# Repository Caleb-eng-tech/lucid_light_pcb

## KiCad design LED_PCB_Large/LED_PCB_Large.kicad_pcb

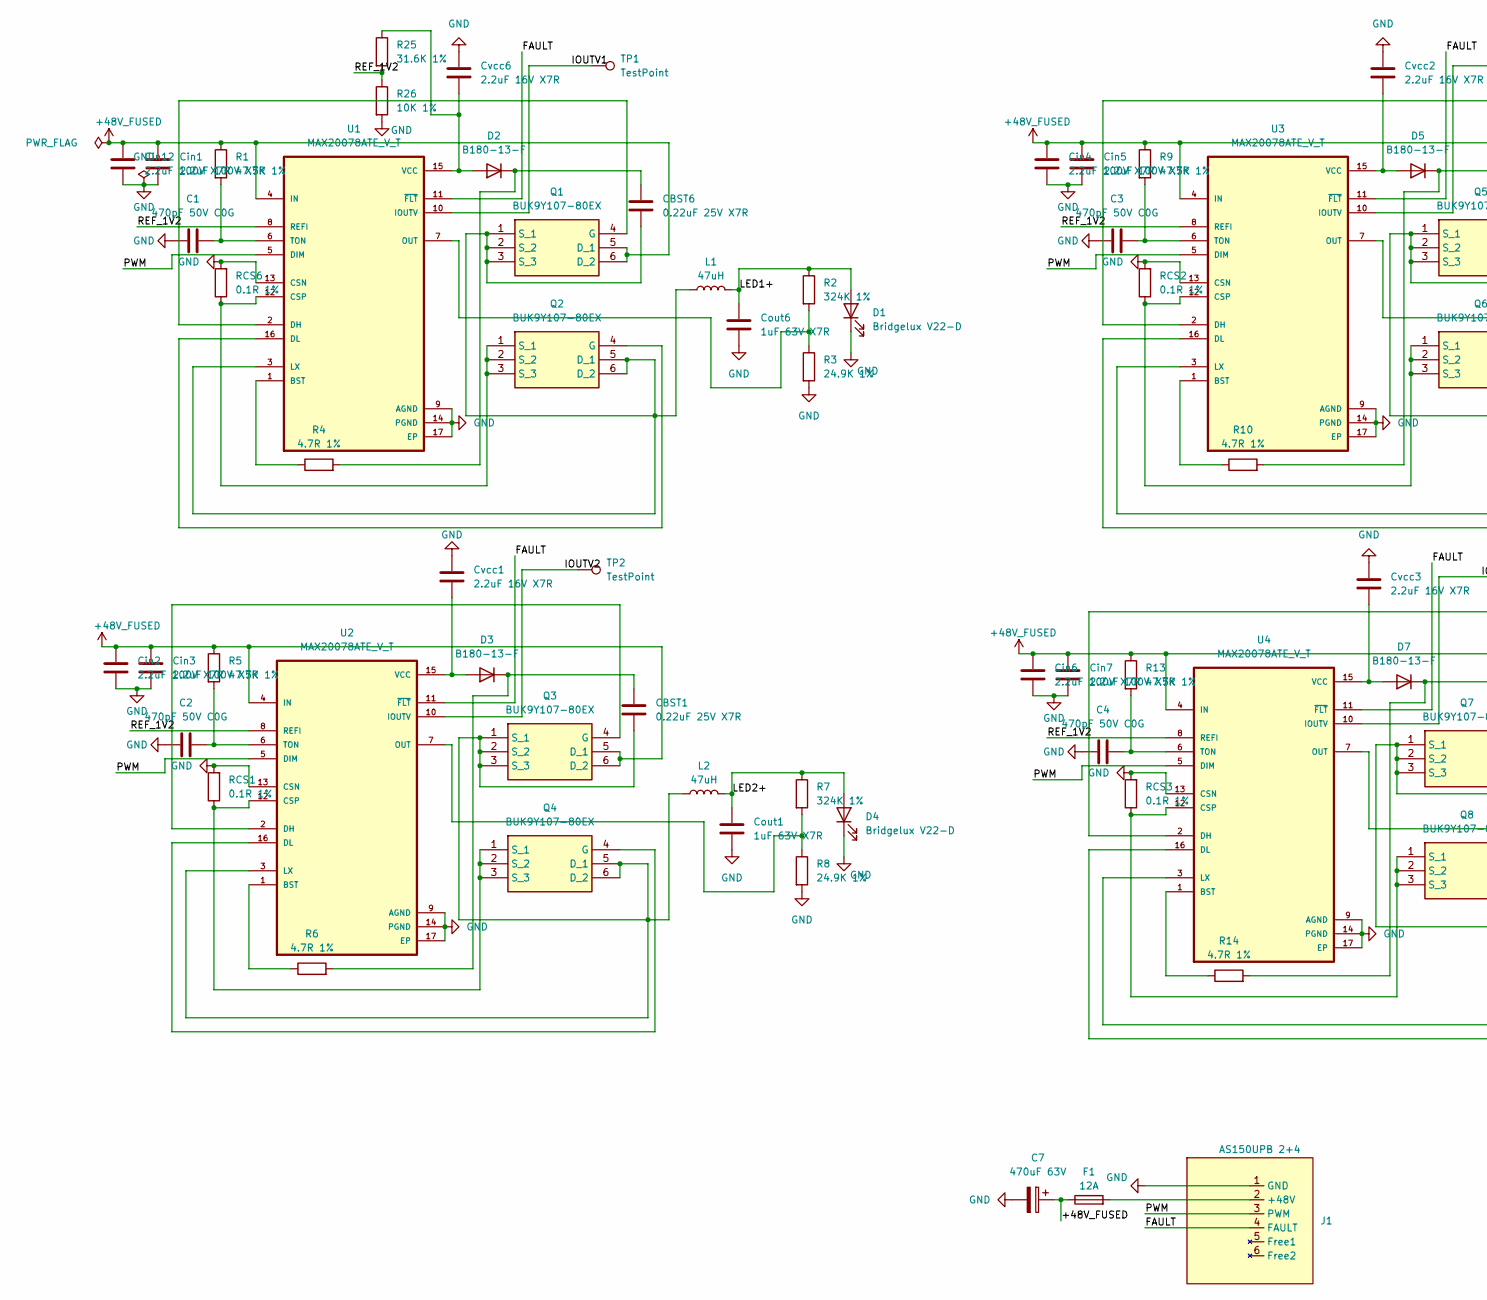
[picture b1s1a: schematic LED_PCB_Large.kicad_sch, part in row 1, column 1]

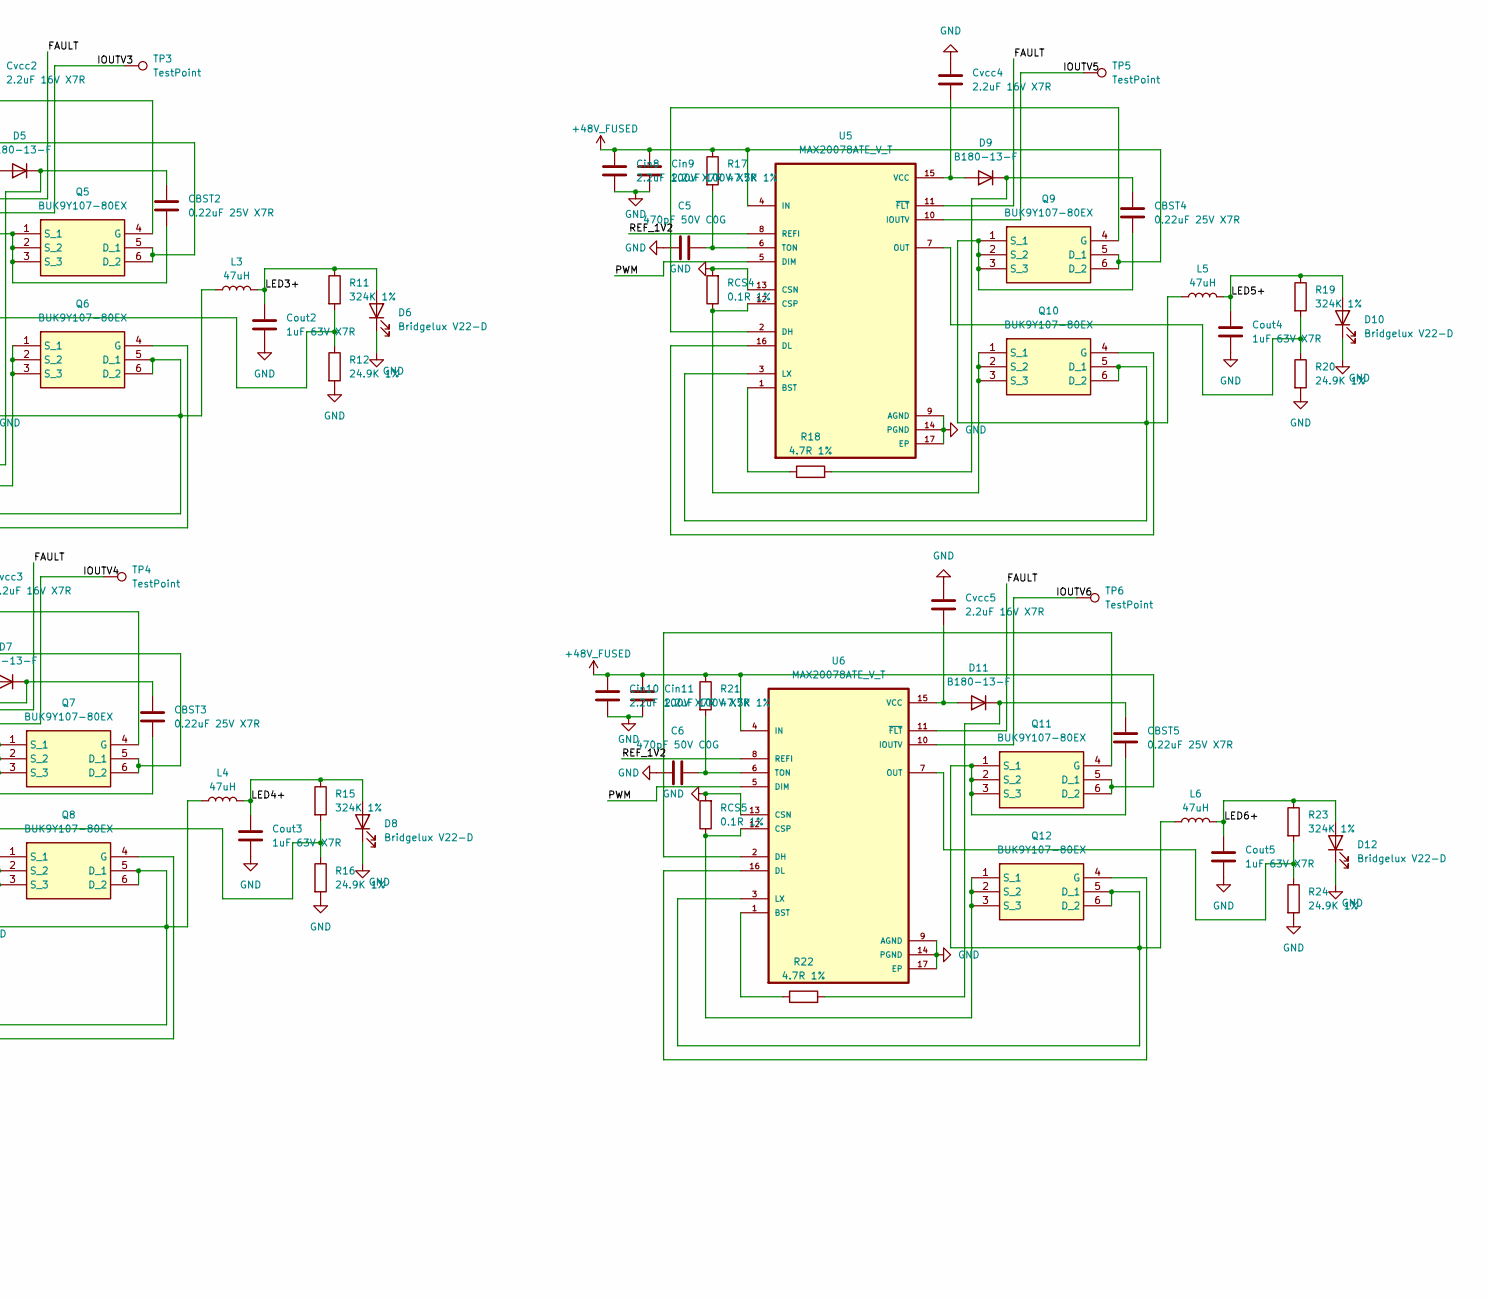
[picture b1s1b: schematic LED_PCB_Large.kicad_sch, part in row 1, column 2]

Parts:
C1, C2, C3, C4, C5, C6: 470pF 50V C0G; C_0603_1608Metric
C7: 470uF 63V; CP_Radial_D12.5mm_P5.00mm
CBST1, CBST2, CBST3, CBST4, CBST5, CBST6: 0.22uF 25V X7R; C_0603_1608Metric
Cin1, Cin2, Cin3, Cin4, Cin5, Cin6, Cin7, Cin8, Cin9, Cin10, Cin11, Cin12: 2.2uF 100V X7R; C_1210_3225Metric
Cout1, Cout2, Cout3, Cout4, Cout5, Cout6: 1uF 63V X7R; C_0805_2012Metric
Cvcc1, Cvcc2, Cvcc3, Cvcc4, Cvcc5, Cvcc6: 2.2uF 16V X7R; C_0805_2012Metric
D1, D4, D6, D8, D10, D12: Bridgelux V22-D; Bridgelux_V22_Custom
D2, D3, D5, D7, D9, D11: B180-13-F; D_SMA
F1: 12A; 0454012.MR
J1: AS150UPB 2+4; AS150UPB_2+4
L1, L2, L3, L4, L5, L6: 47uH; L_Coilcraft_MSS1278T-XXX
Q1, Q2, Q3, Q4, Q5, Q6, Q7, Q8, Q9, Q10, Q11, Q12: BUK9Y107-80EX; PHPT61002NYCLHX; Manufacturer_Part_Number BUK9Y107-80EX; Mouser Part Number 771-BUK9Y107-80EX
R1, R5, R9, R13, R17, R21: 47.5K 1%; R_0603_1608Metric
R2, R7, R11, R15, R19, R23: 324K 1%; R_0603_1608Metric
R3, R8, R12, R16, R20, R24: 24.9K 1%; R_0603_1608Metric
R4, R6, R10, R14, R18, R22: 4.7R 1%; R_0603_1608Metric
R25: 31.6K 1%; R_0603_1608Metric
R26: 10K 1%; R_0603_1608Metric
RCS1, RCS2, RCS3, RCS4, RCS5, RCS6: 0.1R 1%; R_1206_3216Metric
TP1, TP2, TP3, TP4, TP5, TP6: TestPoint; TestPoint_Pad_D1.0mm
U1, U2, U3, U4, U5, U6: MAX20078ATE_V_T; QFN50P300X300X80-17N

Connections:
+48V_FUSED: C7.1, Cin1.1, Cin2.1, Cin3.1, Cin4.1, Cin5.1, Cin6.1, Cin7.1, Cin8.1, Cin9.1, Cin10.1, Cin11.1, Cin12.1, F1.1, Q1.5 (D_1), Q1.6 (D_2), Q3.5 (D_1), Q3.6 (D_2), Q5.5 (D_1), Q5.6 (D_2), Q7.5 (D_1), Q7.6 (D_2), Q9.5 (D_1), Q9.6 (D_2), Q11.5 (D_1), Q11.6 (D_2), R1.1, R5.1, R9.1, R13.1, R17.1, R21.1, U1.4 (IN), U2.4 (IN), U3.4 (IN), U4.4 (IN), U5.4 (IN), U6.4 (IN)
/FAULT: J1.4 (FAULT), U1.11 (~FLT), U2.11 (~FLT), U3.11 (~FLT), U4.11 (~FLT), U5.11 (~FLT), U6.11 (~FLT)
/IOUTV1: TP1.1 (1_1), U1.10 (IOUTV)
/IOUTV2: TP2.1 (1_1), U2.10 (IOUTV)
/IOUTV3: TP3.1 (1_1), U3.10 (IOUTV)
/IOUTV4: TP4.1 (1_1), U4.10 (IOUTV)
/IOUTV5: TP5.1 (1_1), U5.10 (IOUTV)
/IOUTV6: TP6.1 (1_1), U6.10 (IOUTV)
/LED1+: Cout6.1, D1.2 (A), L1.2, R2.1
/LED2+: Cout1.1, D4.2 (A), L2.2, R7.1
/LED3+: Cout2.1, D6.2 (A), L3.2, R11.1
/LED4+: Cout3.1, D8.2 (A), L4.2, R15.1
/LED5+: Cout4.1, D10.2 (A), L5.2, R19.1
/LED6+: Cout5.1, D12.2 (A), L6.2, R23.1
/PWM: J1.3 (PWM), U1.5 (DIM), U2.5 (DIM), U3.5 (DIM), U4.5 (DIM), U5.5 (DIM), U6.5 (DIM)
/REF_1V2: R25.2, R26.1, U1.8 (REFI), U2.8 (REFI), U3.8 (REFI), U4.8 (REFI), U5.8 (REFI), U6.8 (REFI)
GND: C1.1, C2.1, C3.1, C4.1, C5.1, C6.1, C7.2, Cin1.2, Cin2.2, Cin3.2, Cin4.2, Cin5.2, Cin6.2, Cin7.2, Cin8.2, Cin9.2, Cin10.2, Cin11.2, Cin12.2, Cout1.2, Cout2.2, Cout3.2, Cout4.2, Cout5.2, Cout6.2, Cvcc1.1, Cvcc2.1, Cvcc3.1, Cvcc4.1, Cvcc5.1, Cvcc6.1, D1.1 (K), D4.1 (K), D6.1 (K), D8.1 (K), D10.1 (K), D12.1 (K), J1.1 (GND), R3.2, R8.2, R12.2, R16.2, R20.2, R24.2, R26.2, RCS1.2, RCS2.2, RCS3.2, RCS4.2, RCS5.2, RCS6.2, U1.9 (AGND), U1.13 (CSN), U1.14 (PGND), U1.17 (EP), U2.9 (AGND), U2.13 (CSN), U2.14 (PGND), U2.17 (EP), U3.9 (AGND), U3.13 (CSN), U3.14 (PGND), U3.17 (EP), U4.9 (AGND), U4.13 (CSN), U4.14 (PGND), U4.17 (EP), U5.9 (AGND), U5.13 (CSN), U5.14 (PGND), U5.17 (EP), U6.9 (AGND), U6.13 (CSN), U6.14 (PGND), U6.17 (EP)
unnamed: Cvcc6.2, D2.2 (A), R25.1, U1.15 (VCC)
unnamed: CBST6.1, D2.1 (K), R4.2
unnamed: Cvcc1.2, D3.2 (A), U2.15 (VCC)
unnamed: CBST1.1, D3.1 (K), R6.2
unnamed: Cvcc2.2, D5.2 (A), U3.15 (VCC)
unnamed: CBST2.1, D5.1 (K), R10.2
unnamed: Cvcc3.2, D7.2 (A), U4.15 (VCC)
unnamed: CBST3.1, D7.1 (K), R14.2
unnamed: Cvcc4.2, D9.2 (A), U5.15 (VCC)
unnamed: CBST4.1, D9.1 (K), R18.2
unnamed: Cvcc5.2, D11.2 (A), U6.15 (VCC)
unnamed: CBST5.1, D11.1 (K), R22.2
unnamed: F1.2, J1.2 (+48V)
unnamed: Q1.4 (G), U1.2 (DH)
unnamed: CBST6.2, L1.1, Q1.1 (S_1), Q1.2 (S_2), Q1.3 (S_3), Q2.5 (D_1), Q2.6 (D_2), U1.3 (LX)
unnamed: Q2.4 (G), U1.16 (DL)
unnamed: Q2.1 (S_1), Q2.2 (S_2), Q2.3 (S_3), RCS6.1, U1.12 (CSP)
unnamed: Q3.4 (G), U2.2 (DH)
unnamed: CBST1.2, L2.1, Q3.1 (S_1), Q3.2 (S_2), Q3.3 (S_3), Q4.5 (D_1), Q4.6 (D_2), U2.3 (LX)
unnamed: Q4.4 (G), U2.16 (DL)
unnamed: Q4.1 (S_1), Q4.2 (S_2), Q4.3 (S_3), RCS1.1, U2.12 (CSP)
unnamed: Q5.4 (G), U3.2 (DH)
unnamed: CBST2.2, L3.1, Q5.1 (S_1), Q5.2 (S_2), Q5.3 (S_3), Q6.5 (D_1), Q6.6 (D_2), U3.3 (LX)
unnamed: Q6.4 (G), U3.16 (DL)
unnamed: Q6.1 (S_1), Q6.2 (S_2), Q6.3 (S_3), RCS2.1, U3.12 (CSP)
unnamed: Q7.4 (G), U4.2 (DH)
unnamed: CBST3.2, L4.1, Q7.1 (S_1), Q7.2 (S_2), Q7.3 (S_3), Q8.5 (D_1), Q8.6 (D_2), U4.3 (LX)
unnamed: Q8.4 (G), U4.16 (DL)
unnamed: Q8.1 (S_1), Q8.2 (S_2), Q8.3 (S_3), RCS3.1, U4.12 (CSP)
unnamed: Q9.4 (G), U5.2 (DH)
unnamed: CBST4.2, L5.1, Q9.1 (S_1), Q9.2 (S_2), Q9.3 (S_3), Q10.5 (D_1), Q10.6 (D_2), U5.3 (LX)
unnamed: Q10.4 (G), U5.16 (DL)
unnamed: Q10.1 (S_1), Q10.2 (S_2), Q10.3 (S_3), RCS4.1, U5.12 (CSP)
unnamed: Q11.4 (G), U6.2 (DH)
unnamed: CBST5.2, L6.1, Q11.1 (S_1), Q11.2 (S_2), Q11.3 (S_3), Q12.5 (D_1), Q12.6 (D_2), U6.3 (LX)
unnamed: Q12.4 (G), U6.16 (DL)
unnamed: Q12.1 (S_1), Q12.2 (S_2), Q12.3 (S_3), RCS5.1, U6.12 (CSP)
unnamed: R4.1, U1.1 (BST)
unnamed: R2.2, R3.1, U1.7 (OUT)
unnamed: C1.2, R1.2, U1.6 (TON)
unnamed: R6.1, U2.1 (BST)
unnamed: R7.2, R8.1, U2.7 (OUT)
unnamed: C2.2, R5.2, U2.6 (TON)
unnamed: R10.1, U3.1 (BST)
unnamed: R11.2, R12.1, U3.7 (OUT)
unnamed: C3.2, R9.2, U3.6 (TON)
unnamed: R14.1, U4.1 (BST)
unnamed: R15.2, R16.1, U4.7 (OUT)
unnamed: C4.2, R13.2, U4.6 (TON)
unnamed: R18.1, U5.1 (BST)
unnamed: R19.2, R20.1, U5.7 (OUT)
unnamed: C5.2, R17.2, U5.6 (TON)
unnamed: R22.1, U6.1 (BST)
unnamed: R23.2, R24.1, U6.7 (OUT)
unnamed: C6.2, R21.2, U6.6 (TON)

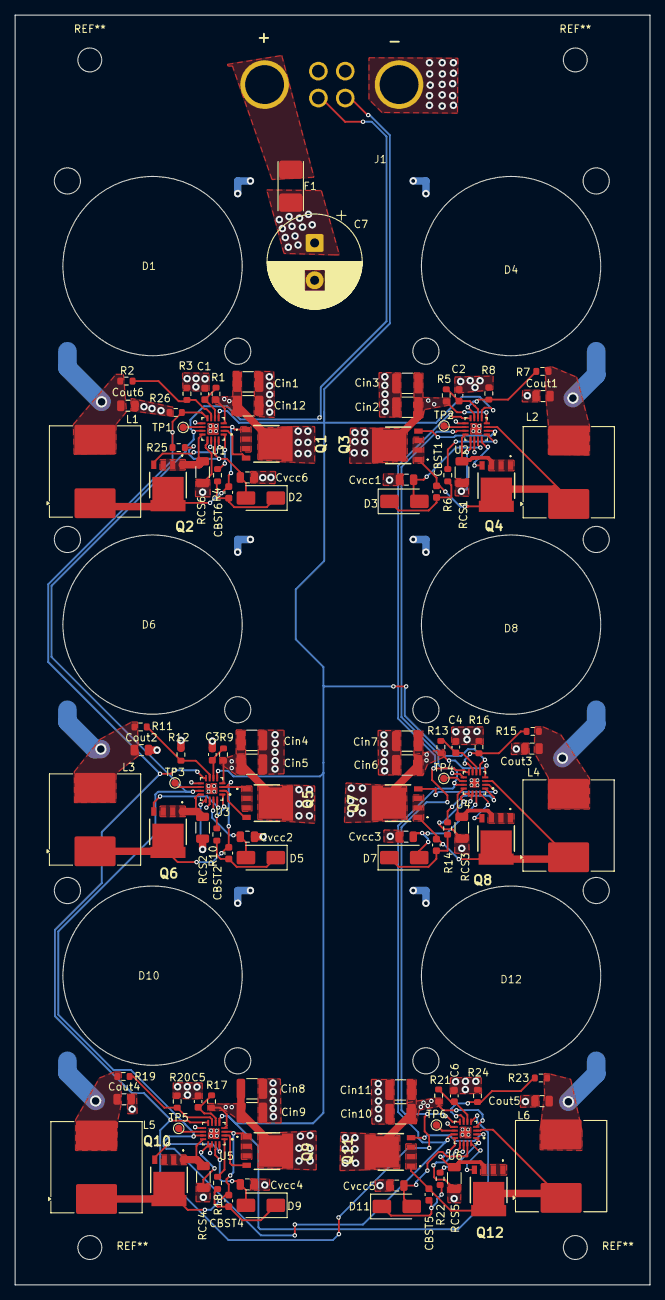
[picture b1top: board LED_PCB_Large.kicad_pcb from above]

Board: 4 copper layers, 85.0 x 170.0 mm, 113 parts (0 on the bottom side), 72 nets.

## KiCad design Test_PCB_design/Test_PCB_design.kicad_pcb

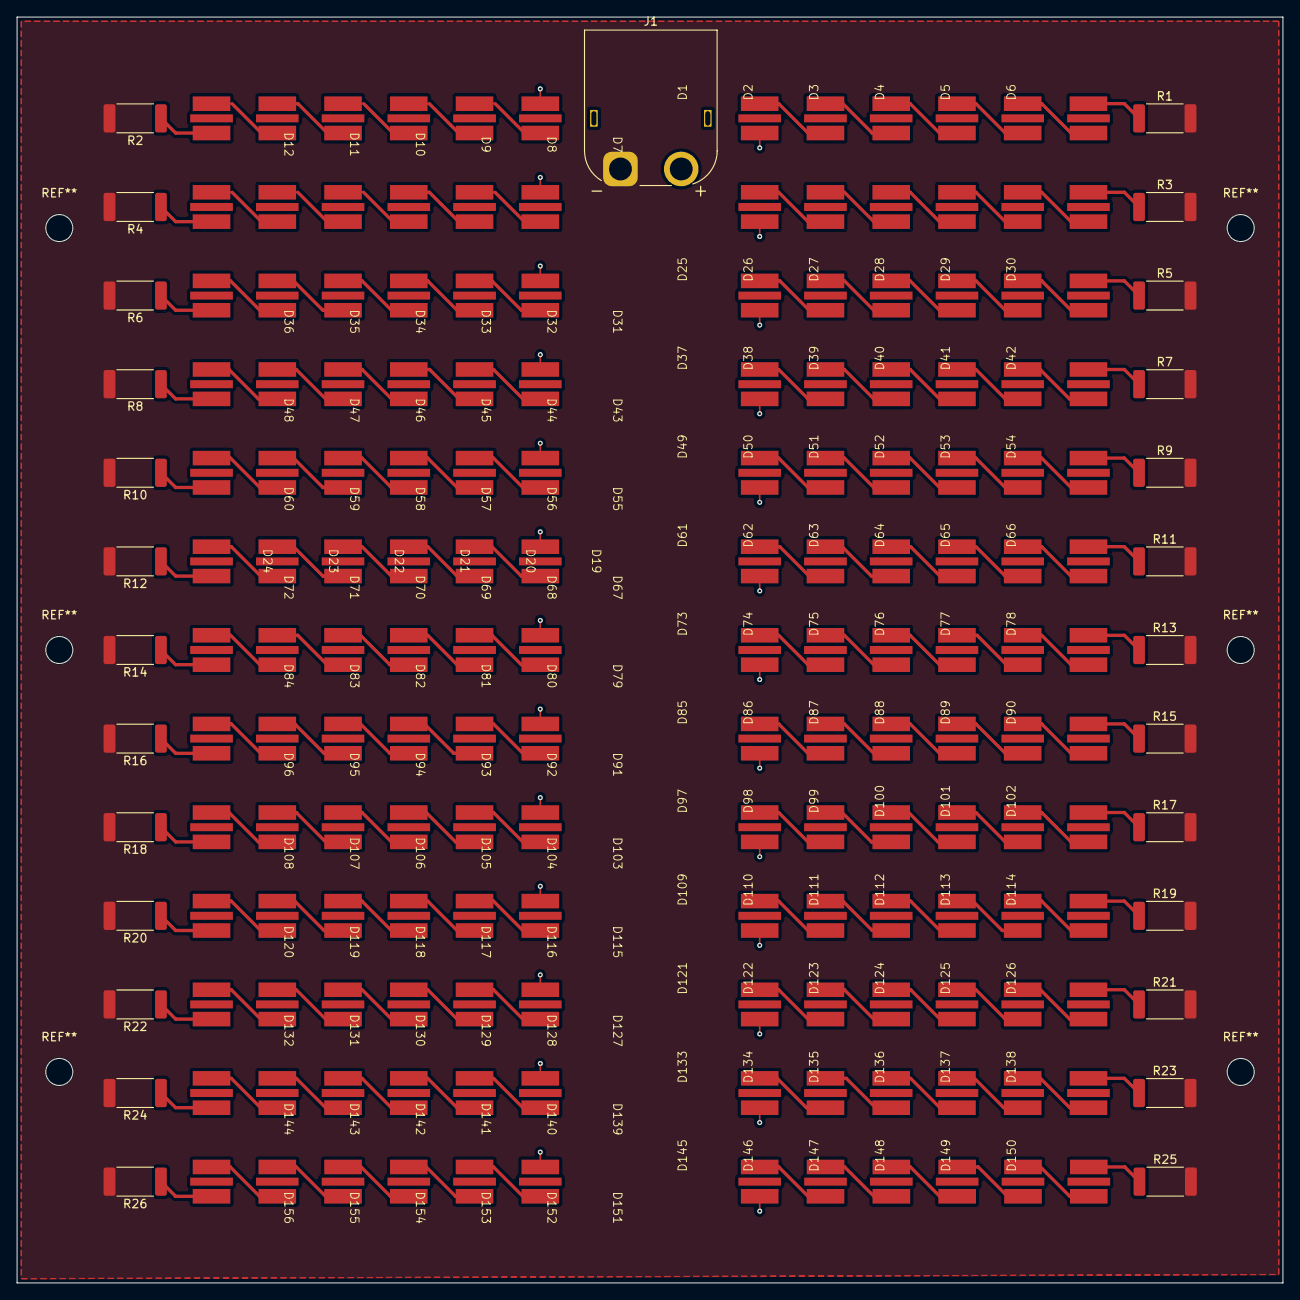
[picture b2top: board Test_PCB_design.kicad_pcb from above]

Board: 2 copper layers, 150.0 x 150.0 mm, 183 parts (0 on the bottom side), 158 nets.

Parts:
D1, D2, D3, D4, D5, D6, D7, D8, D9, D10, D11, D12, D13, D14, D15, D16, D17, D18, D19, D20, D21, D22, D23, D24, D25, D26, D27, D28, D29, D30, D31, D32, D33, D34, D35, D36, D37, D38, D39, D40, D41, D42, D43, D44, D45, D46, D47, D48, D49, D50, D51, D52, D53, D54, D55, D56, D57, D58, D59, D60, D61, D62, D63, D64, D65, D66, D67, D68, D69, D70, D71, D72, D73, D74, D75, D76, D77, D78, D79, D80, D81, D82, D83, D84, D85, D86, D87, D88, D89, D90, D91, D92, D93, D94, D95, D96, D97, D98, D99, D100, D101, D102, D103, D104, D105, D106, D107, D108, D109, D110, D111, D112, D113, D114, D115, D116, D117, D118, D119, D120, D121, D122, D123, D124, D125, D126, D127, D128, D129, D130, D131, D132, D133, D134, D135, D136, D137, D138, D139, D140, D141, D142, D143, D144, D145, D146, D147, D148, D149, D150, D151, D152, D153, D154, D155, D156: Cree_JR5050C
J1: Conn_01x02_Pin; AMASS_XT60PW-M_1x02_P7.20mm_Horizontal
R1, R2, R3, R4, R5, R6, R7, R8, R9, R10, R11, R12, R13, R14, R15, R16, R17, R18, R19, R20, R21, R22, R23, R24, R25, R26: 2R; R_2512_6332Metric_Pad1.40x3.35mm_HandSolder

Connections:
/LED+: J1.1, R1.2, R2.2, R3.2, R4.2, R5.2, R6.2, R7.2, R8.2, R9.2, R10.2, R11.2, R12.2, R13.2, R14.2, R15.2, R16.2, R17.2, R18.2, R19.2, R20.2, R21.2, R22.2, R23.2, R24.2, R25.2, R26.2
/LED-: D1.1 (K), D7.1 (K), D13.1 (K), D19.1 (K), D25.1 (K), D31.1 (K), D37.1 (K), D43.1 (K), D49.1 (K), D55.1 (K), D61.1 (K), D67.1 (K), D73.1 (K), D79.1 (K), D85.1 (K), D91.1 (K), D97.1 (K), D103.1 (K), D109.1 (K), D115.1 (K), D121.1 (K), D127.1 (K), D133.1 (K), D139.1 (K), D145.1 (K), D151.1 (K), J1.2
unnamed: D1.2 (A), D2.1 (K)
unnamed: D2.2 (A), D3.1 (K)
unnamed: D3.2 (A), D4.1 (K)
unnamed: D4.2 (A), D5.1 (K)
unnamed: D5.2 (A), D6.1 (K)
unnamed: D6.2 (A), R1.1
unnamed: D7.2 (A), D8.1 (K)
unnamed: D8.2 (A), D9.1 (K)
unnamed: D10.2 (A), D11.1 (K)
unnamed: D9.2 (A), D10.1 (K)
unnamed: D11.2 (A), D12.1 (K)
unnamed: D12.2 (A), R2.1
unnamed: D13.2 (A), D14.1 (K)
unnamed: D14.2 (A), D15.1 (K)
unnamed: D15.2 (A), D16.1 (K)
unnamed: D16.2 (A), D17.1 (K)
unnamed: D17.2 (A), D18.1 (K)
unnamed: D18.2 (A), R3.1
unnamed: D19.2 (A), D20.1 (K)
unnamed: D20.2 (A), D21.1 (K)
unnamed: D21.2 (A), D22.1 (K)
unnamed: D22.2 (A), D23.1 (K)
unnamed: D23.2 (A), D24.1 (K)
unnamed: D24.2 (A), R4.1
unnamed: D25.2 (A), D26.1 (K)
unnamed: D26.2 (A), D27.1 (K)
unnamed: D27.2 (A), D28.1 (K)
unnamed: D28.2 (A), D29.1 (K)
unnamed: D29.2 (A), D30.1 (K)
unnamed: D30.2 (A), R5.1
unnamed: D31.2 (A), D32.1 (K)
unnamed: D32.2 (A), D33.1 (K)
unnamed: D33.2 (A), D34.1 (K)
unnamed: D34.2 (A), D35.1 (K)
unnamed: D35.2 (A), D36.1 (K)
unnamed: D36.2 (A), R6.1
unnamed: D37.2 (A), D38.1 (K)
unnamed: D38.2 (A), D39.1 (K)
unnamed: D39.2 (A), D40.1 (K)
unnamed: D40.2 (A), D41.1 (K)
unnamed: D41.2 (A), D42.1 (K)
unnamed: D42.2 (A), R7.1
unnamed: D43.2 (A), D44.1 (K)
unnamed: D44.2 (A), D45.1 (K)
unnamed: D45.2 (A), D46.1 (K)
unnamed: D46.2 (A), D47.1 (K)
unnamed: D47.2 (A), D48.1 (K)
unnamed: D48.2 (A), R8.1
unnamed: D49.2 (A), D50.1 (K)
unnamed: D50.2 (A), D51.1 (K)
unnamed: D51.2 (A), D52.1 (K)
unnamed: D52.2 (A), D53.1 (K)
unnamed: D53.2 (A), D54.1 (K)
unnamed: D54.2 (A), R9.1
unnamed: D55.2 (A), D56.1 (K)
unnamed: D56.2 (A), D57.1 (K)
unnamed: D57.2 (A), D58.1 (K)
unnamed: D58.2 (A), D59.1 (K)
unnamed: D59.2 (A), D60.1 (K)
unnamed: D60.2 (A), R10.1
unnamed: D61.2 (A), D62.1 (K)
unnamed: D62.2 (A), D63.1 (K)
unnamed: D63.2 (A), D64.1 (K)
unnamed: D64.2 (A), D65.1 (K)
unnamed: D65.2 (A), D66.1 (K)
unnamed: D66.2 (A), R11.1
unnamed: D67.2 (A), D68.1 (K)
unnamed: D68.2 (A), D69.1 (K)
unnamed: D69.2 (A), D70.1 (K)
unnamed: D70.2 (A), D71.1 (K)
unnamed: D71.2 (A), D72.1 (K)
unnamed: D72.2 (A), R12.1
unnamed: D73.2 (A), D74.1 (K)
unnamed: D74.2 (A), D75.1 (K)
unnamed: D75.2 (A), D76.1 (K)
unnamed: D76.2 (A), D77.1 (K)
unnamed: D77.2 (A), D78.1 (K)
unnamed: D78.2 (A), R13.1
unnamed: D79.2 (A), D80.1 (K)
unnamed: D80.2 (A), D81.1 (K)
unnamed: D81.2 (A), D82.1 (K)
unnamed: D82.2 (A), D83.1 (K)
unnamed: D83.2 (A), D84.1 (K)
unnamed: D84.2 (A), R14.1
unnamed: D85.2 (A), D86.1 (K)
unnamed: D86.2 (A), D87.1 (K)
unnamed: D87.2 (A), D88.1 (K)
unnamed: D88.2 (A), D89.1 (K)
unnamed: D89.2 (A), D90.1 (K)
unnamed: D90.2 (A), R15.1
unnamed: D91.2 (A), D92.1 (K)
unnamed: D92.2 (A), D93.1 (K)
unnamed: D93.2 (A), D94.1 (K)
unnamed: D94.2 (A), D95.1 (K)
unnamed: D95.2 (A), D96.1 (K)
unnamed: D96.2 (A), R16.1
unnamed: D97.2 (A), D98.1 (K)
unnamed: D98.2 (A), D99.1 (K)
unnamed: D100.2 (A), D101.1 (K)
unnamed: D99.2 (A), D100.1 (K)
unnamed: D101.2 (A), D102.1 (K)
unnamed: D102.2 (A), R17.1
unnamed: D103.2 (A), D104.1 (K)
unnamed: D104.2 (A), D105.1 (K)
unnamed: D105.2 (A), D106.1 (K)
unnamed: D106.2 (A), D107.1 (K)
unnamed: D107.2 (A), D108.1 (K)
unnamed: D108.2 (A), R18.1
unnamed: D109.2 (A), D110.1 (K)
unnamed: D110.2 (A), D111.1 (K)
unnamed: D111.2 (A), D112.1 (K)
unnamed: D112.2 (A), D113.1 (K)
unnamed: D113.2 (A), D114.1 (K)
unnamed: D114.2 (A), R19.1
unnamed: D115.2 (A), D116.1 (K)
unnamed: D116.2 (A), D117.1 (K)
unnamed: D117.2 (A), D118.1 (K)
unnamed: D118.2 (A), D119.1 (K)
unnamed: D119.2 (A), D120.1 (K)
unnamed: D120.2 (A), R20.1
unnamed: D121.2 (A), D122.1 (K)
unnamed: D122.2 (A), D123.1 (K)
unnamed: D123.2 (A), D124.1 (K)
unnamed: D124.2 (A), D125.1 (K)
unnamed: D125.2 (A), D126.1 (K)
unnamed: D126.2 (A), R21.1
unnamed: D127.2 (A), D128.1 (K)
unnamed: D128.2 (A), D129.1 (K)
unnamed: D129.2 (A), D130.1 (K)
unnamed: D130.2 (A), D131.1 (K)
unnamed: D131.2 (A), D132.1 (K)
unnamed: D132.2 (A), R22.1
unnamed: D133.2 (A), D134.1 (K)
unnamed: D134.2 (A), D135.1 (K)
unnamed: D135.2 (A), D136.1 (K)
unnamed: D136.2 (A), D137.1 (K)
unnamed: D137.2 (A), D138.1 (K)
unnamed: D138.2 (A), R23.1
unnamed: D139.2 (A), D140.1 (K)
unnamed: D140.2 (A), D141.1 (K)
unnamed: D141.2 (A), D142.1 (K)
unnamed: D142.2 (A), D143.1 (K)
unnamed: D143.2 (A), D144.1 (K)
unnamed: D144.2 (A), R24.1
unnamed: D145.2 (A), D146.1 (K)
unnamed: D146.2 (A), D147.1 (K)
unnamed: D147.2 (A), D148.1 (K)
unnamed: D148.2 (A), D149.1 (K)
unnamed: D149.2 (A), D150.1 (K)
unnamed: D150.2 (A), R25.1
unnamed: D151.2 (A), D152.1 (K)
unnamed: D152.2 (A), D153.1 (K)
unnamed: D153.2 (A), D154.1 (K)
unnamed: D154.2 (A), D155.1 (K)
unnamed: D155.2 (A), D156.1 (K)
unnamed: D156.2 (A), R26.1
